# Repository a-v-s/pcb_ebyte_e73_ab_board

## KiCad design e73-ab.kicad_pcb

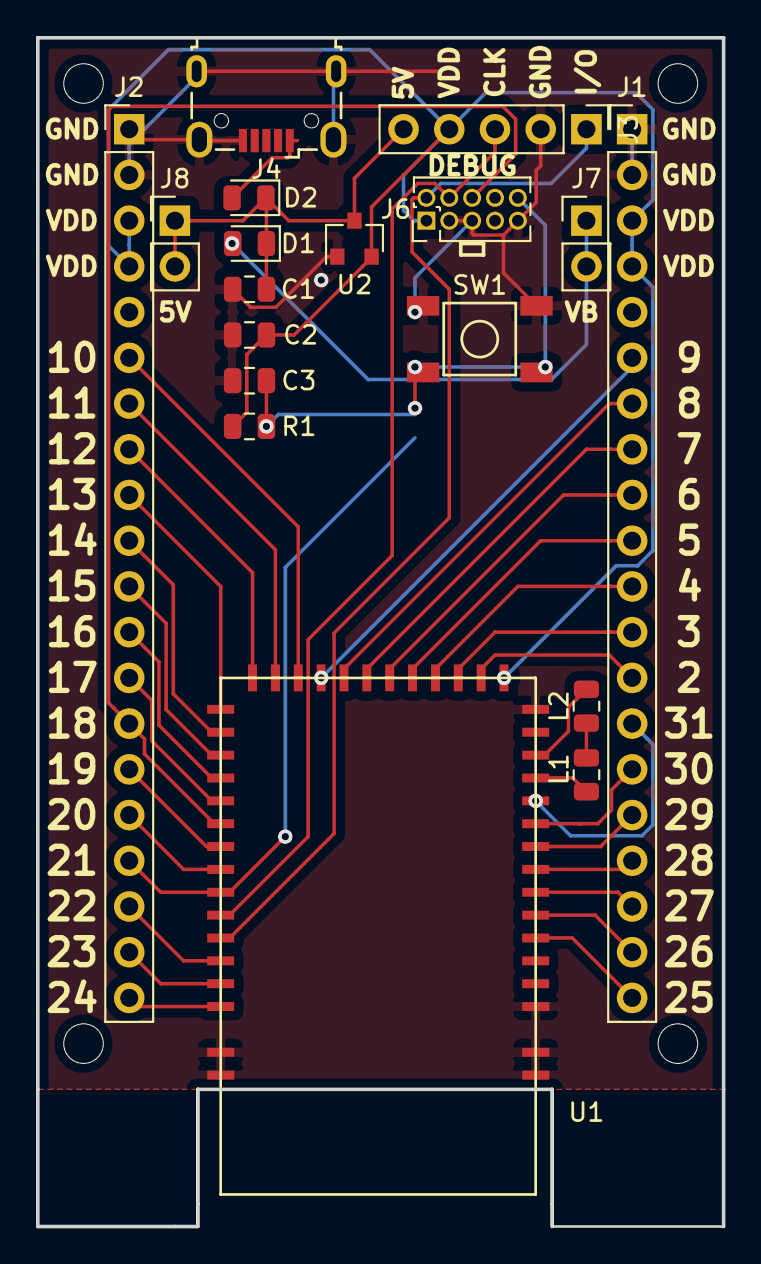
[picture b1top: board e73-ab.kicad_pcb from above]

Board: 2 copper layers, 38.1 x 66.0 mm, 23 parts (1 on the bottom side), 41 nets.

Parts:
C1: 1u; C_0805_2012Metric
C2: 2u2; C_0805_2012Metric
C3: CP_Small; C_0805_2012Metric
D1, D2: D_Schottky; D_0805_2012Metric
H1, H2, H3, H4: MountingHole; MountingHole_2.2mm_M2_ISO7380
J1, J2: Conn_01x20_Male; PinHeader_1x20_P2.54mm_Vertical
J3: Conn_01x04_Male; PinHeader_1x05_P2.54mm_Vertical
J4: USB_B_Micro; USB_Micro-B_Wuerth_629105150521
J6: Conn_02x05_Odd_Even; PinHeader_2x05_P1.27mm_Vertical
J7, J8: Conn_02x02_Odd_Even; PinHeader_1x02_P2.54mm_Vertical
JP1: SolderJumper_2_Bridged; SolderJumper-2_P1.3mm_Bridged_RoundedPad1.0x1.5mm
L1: 15n; L_0805_2012Metric
L2: 10u; L_0805_2012Metric
R1: 10K; R_0805_2012Metric
SW1: SW_Push; TS-1187
U1: E73-AB; E73-B
U2: MCP1700-3302E_SOT23; SOT-23

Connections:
2: J1.13, U1.17
3: J1.12, U1.18
4: J1.11, U1.19
5: J1.10, U1.20
5V: C1.1, D1.1, D2.1, J3.5, J8.1, J8.2, U2.3
6: J1.9, U1.21
7: J1.8, U1.22
8: J1.7, U1.23
9: J1.6, U1.24
10: J2.6, U1.25
11: J2.7, U1.26
12: J2.8, U1.27
13: J2.9, U1.28
14: J2.10, U1.29
15: J2.11, U1.30
16: J2.12, U1.31
17: J2.13, U1.32
18: J2.14, J6.6, U1.33
19: J2.15, U1.34
20: J2.16, U1.35
21: J2.17, JP1.1, U1.36
22: J2.18, U1.39
23: J2.19, U1.40
24: J2.20, U1.41
25: J1.20, U1.5
26: J1.19, U1.6
27: J1.18, U1.7
28: J1.17, U1.8
29: J1.16, U1.9
30: J1.15, U1.10
31: J1.14, U1.11
!RST: C3.1, J6.10, JP1.2, R1.2, SW1.1
GND: C1.2, C2.2, C3.2, J1.1, J1.2, J2.1, J2.2, J3.2, J4.5, J4.6, J6.3, J6.5, J6.9, SW1.2, U1.0, U1.1, U1.2, U1.15, U1.42, U1.43, U2.1
unnamed: L1.1, L2.2
unnamed: L1.2, U1.12
unnamed: L2.1, U1.13
SWDCLK: J3.3, J6.4, U1.37
SWDIO: J3.1, J6.2, U1.38
VBAT: D1.2, J7.1, J7.2
VBUS: D2.2, J4.1
VDD: C2.1, J1.3, J1.4, J2.3, J2.4, J3.4, J6.1, R1.1, U1.16, U2.2

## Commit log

2018-11-19 Modified 5V header
2018-11-19 Added fill
2018-11-19 Modified text on the back
2018-11-20 Swapped LDO
2018-12-14 The hole for the antenna wasn't enough, redesign
2018-12-14 Added vdd plane
2018-12-16 Adding diode for vbus
2019-01-03 E73-AB V3
2020-01-04 Gerber
